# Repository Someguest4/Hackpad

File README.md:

<h1>MAC-4:</h1> 

(like a CounterStrike MAC-10 but it has 4 keys to quick buy weapons)

By Andrei Ermolaev

<h2>Inspiration:</h2>

I saw an Instagram Reel on my FYP by willdoesbuild that told me about the Hack Club Blueprint Project. I decided to try it out. *(I hope I get approved.)*

<h2>Challenges:</h2>

This was my first ever Hardware Project. I had to learn how to use Fusion 360 and KiCad. I only had some Blender experience. The Hackpad guide really helped me.
<h2>Specifications:</h2>

4x Cherry MX Switches

2x SK6812 MINI Leds

1x XIAO RP2040

4x Blank DSA Keycaps

4x M3x16 Bolt

4x M3 Heatset

<h3>Case Bottom:</h3>

<h3>Case Top:</h3>

<h3>PCB:</h3>

<h3>Schematic:</h3>

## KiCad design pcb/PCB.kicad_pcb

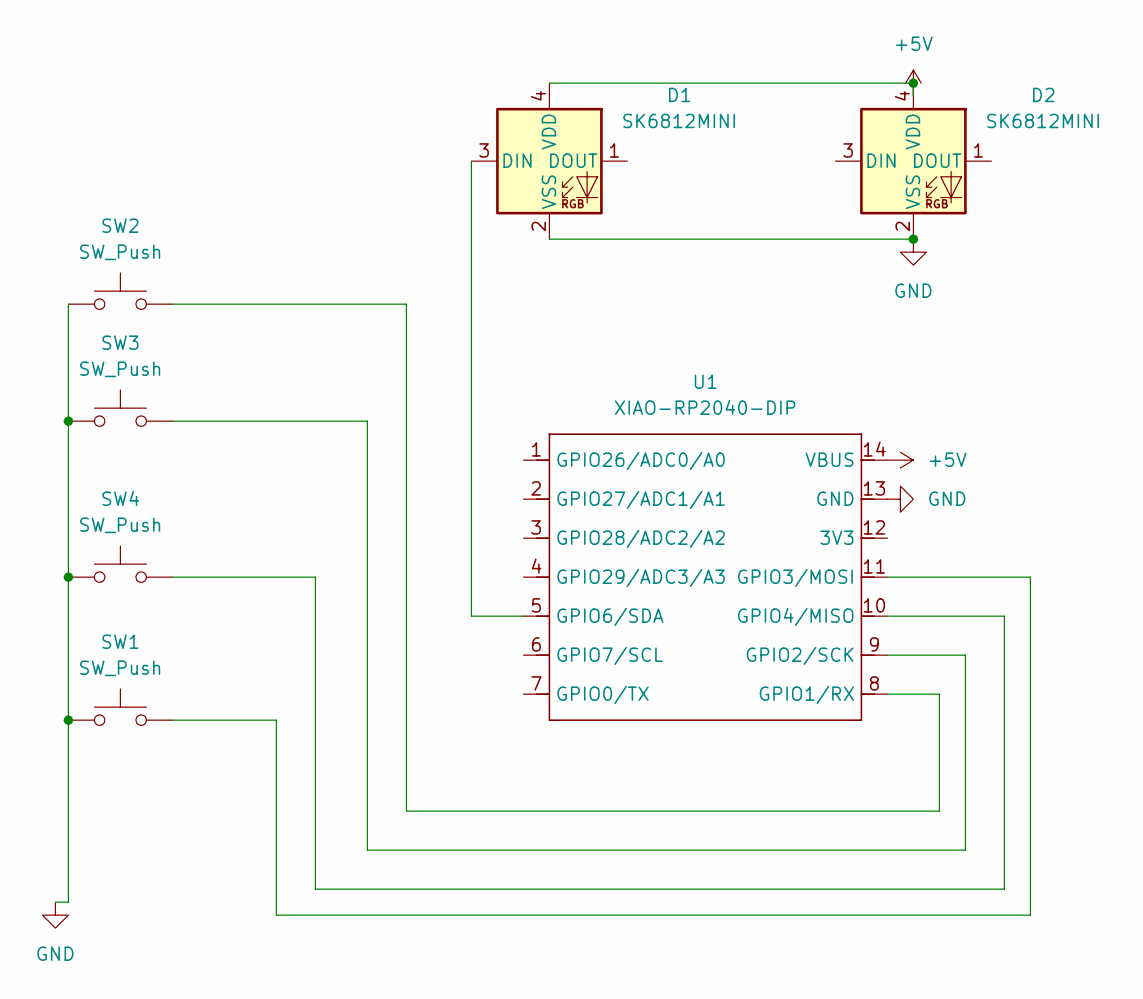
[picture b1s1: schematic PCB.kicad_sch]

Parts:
D1, D2: SK6812MINI; LED_SK6812MINI_PLCC4_3.5x3.5mm_P1.75mm
SW1, SW2, SW3, SW4: SW_Push; SW_Cherry_MX_1.00u_PCB
U1: XIAO-RP2040-DIP

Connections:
+5V: D1.4 (VDD), D2.4 (VDD), U1.14 (VBUS)
GND: D1.2 (VSS), D2.2 (VSS), SW1.1, SW2.1, SW3.1, SW4.1, U1.13 (GND)
unnamed: D1.3 (DIN), U1.5 (GPIO6/SDA)
unnamed: SW2.2, U1.8 (GPIO1/RX)
unnamed: SW3.2, U1.9 (GPIO2/SCK)
unnamed: SW1.2, U1.11 (GPIO3/MOSI)
unnamed: SW4.2, U1.10 (GPIO4/MISO)

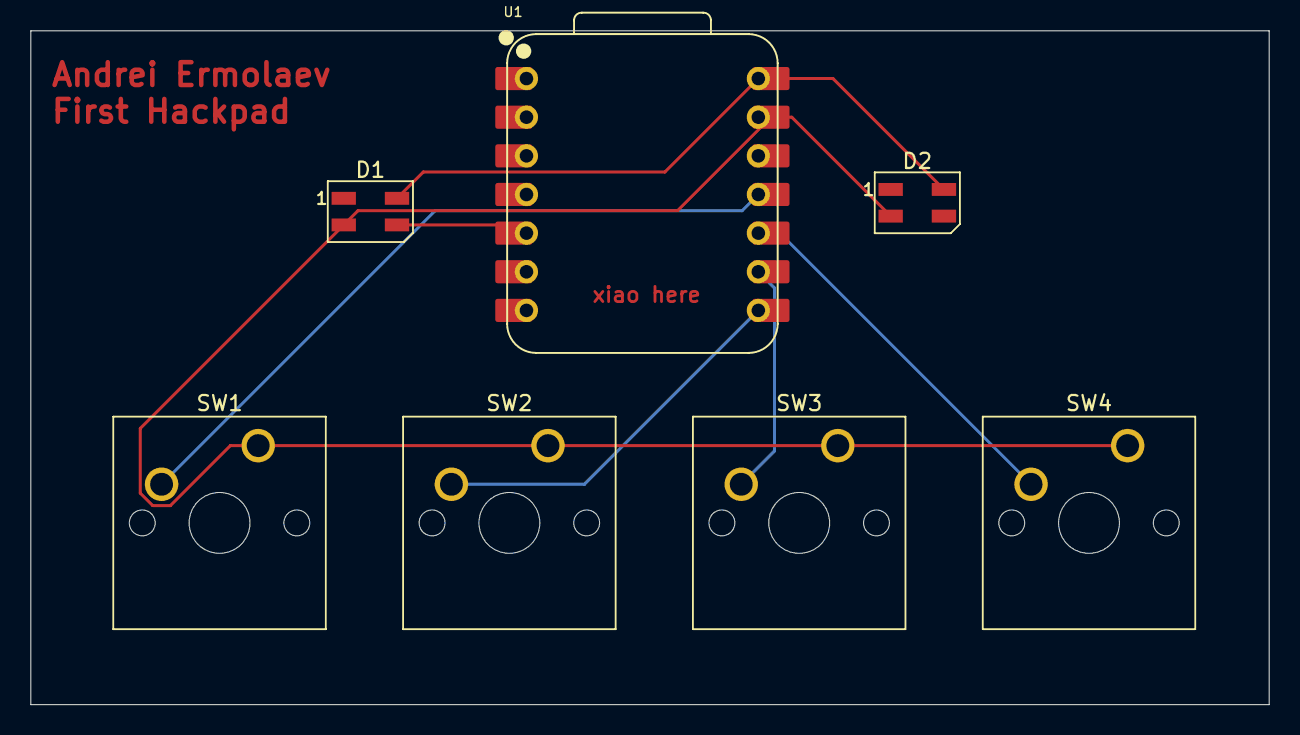
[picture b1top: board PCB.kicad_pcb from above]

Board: 2 copper layers, 81.4 x 44.3 mm, 7 parts (0 on the bottom side), 7 nets.

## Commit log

2025-12-06 6.12.2025
2025-12-07 7.12.2025
